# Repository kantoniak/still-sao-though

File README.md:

# Still SAO though

[SAO (Simple Add-on/Shitty Add-on)](https://hackaday.io/project/52950-shitty-add-ons/log/159806-introducing-the-shitty-add-on-v169bis-standard) board celebrating our _eggcelent_ friends.
As seen at Hackaday Supercon 2024 and Hackaday Europe 2025.

Built around ATTINY85, with two bottom-throwing LEDs. I tried adding I2C support using TinyWire's stack and failed miserably, likely due to [clock stretching](https://en.wikipedia.org/wiki/I²C#Clock_stretching_using_SCL) issues.

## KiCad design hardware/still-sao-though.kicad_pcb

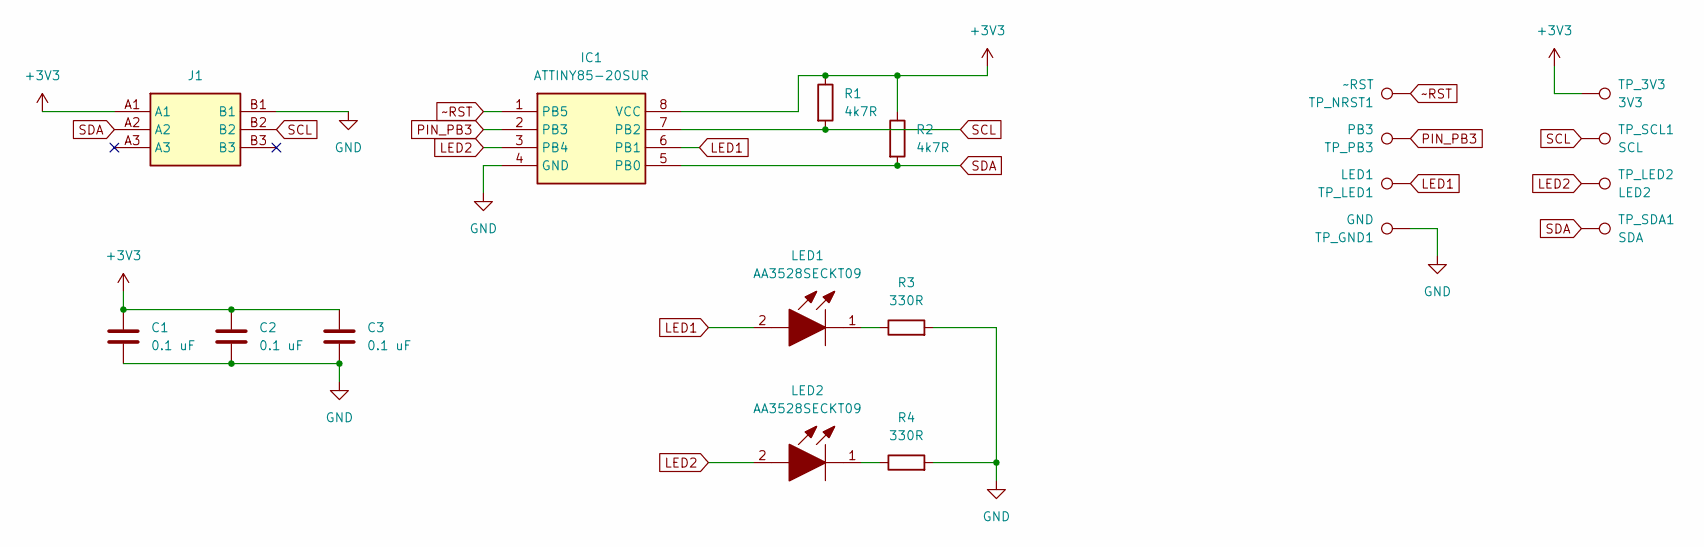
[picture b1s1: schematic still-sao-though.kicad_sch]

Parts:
C1, C2, C3: 0.1 uF; C_0603_1608Metric_Pad1.08x0.95mm_HandSolder
IC1: ATTINY85-20SUR; SOIC127P798X216-8N; Mouser Part Number 556-ATTINY85-20SUR
J1: 10129383-906002BLF; 10129383906002BLF; Manufacturer_Part_Number 10129383-906002BLF
LED1, LED2: AA3528SECKT09; Mouser Part Number 604-AA3528SECKT09
R1, R2: 4k7R; R_0603_1608Metric_Pad0.98x0.95mm_HandSolder
R3, R4: 330R; R_0603_1608Metric_Pad0.98x0.95mm_HandSolder
TP_3V3: 3V3; TestPoint_Pad_D1.0mm
TP_GND1: GND; TestPoint_Pad_D1.0mm
TP_LED1: LED1; TestPoint_Pad_D1.0mm
TP_LED2: LED2; TestPoint_Pad_D1.0mm
TP_NRST1: ~RST; TestPoint_Pad_D1.0mm
TP_PB3: PB3; TestPoint_Pad_D1.0mm
TP_SCL1: SCL; TestPoint_Pad_D1.0mm
TP_SDA1: SDA; TestPoint_Pad_D1.0mm

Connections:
+3V3: C1.1, C2.1, C3.1, IC1.8 (VCC), J1.A1, R1.1, R2.1, TP_3V3.1
GND: C1.2, C2.2, C3.2, IC1.4 (GND), J1.B1, R3.2, R4.2, TP_GND1.1
LED1: IC1.6 (PB1), LED1.2, TP_LED1.1
LED2: IC1.3 (PB4), LED2.2, TP_LED2.1
unnamed: LED1.1, R3.1
unnamed: LED2.1, R4.1
PIN_PB3: IC1.2 (PB3), TP_PB3.1
SCL: IC1.7 (PB2), J1.B2, R1.2, TP_SCL1.1
SDA: IC1.5 (PB0), J1.A2, R2.2, TP_SDA1.1
~RST: IC1.1 (PB5), TP_NRST1.1

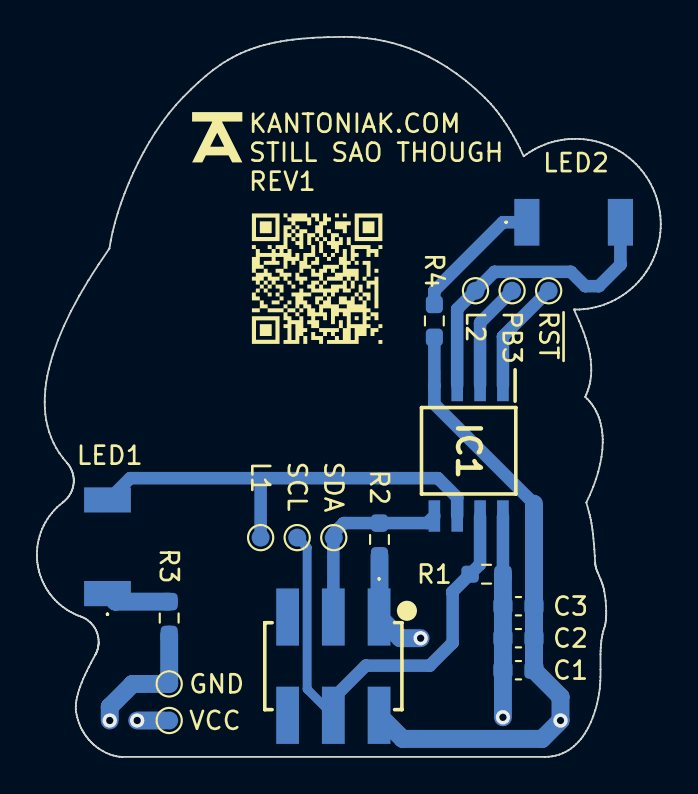
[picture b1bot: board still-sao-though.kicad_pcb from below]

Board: 4 copper layers, 34.7 x 40.0 mm, 19 parts (19 on the bottom side), 10 nets.

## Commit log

2024-10-28 Hello, still-sao-though!
2024-10-28 Fix reference-style link formatting
2025-03-22 Blink LEDs interchangeably
2025-03-22 Add hardware files
